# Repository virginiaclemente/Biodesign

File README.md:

# Biodesign
During the Biodesign course, my team and I developed a syringe infusion pump, a mechatronic device to control the flow rate of drug delivery.

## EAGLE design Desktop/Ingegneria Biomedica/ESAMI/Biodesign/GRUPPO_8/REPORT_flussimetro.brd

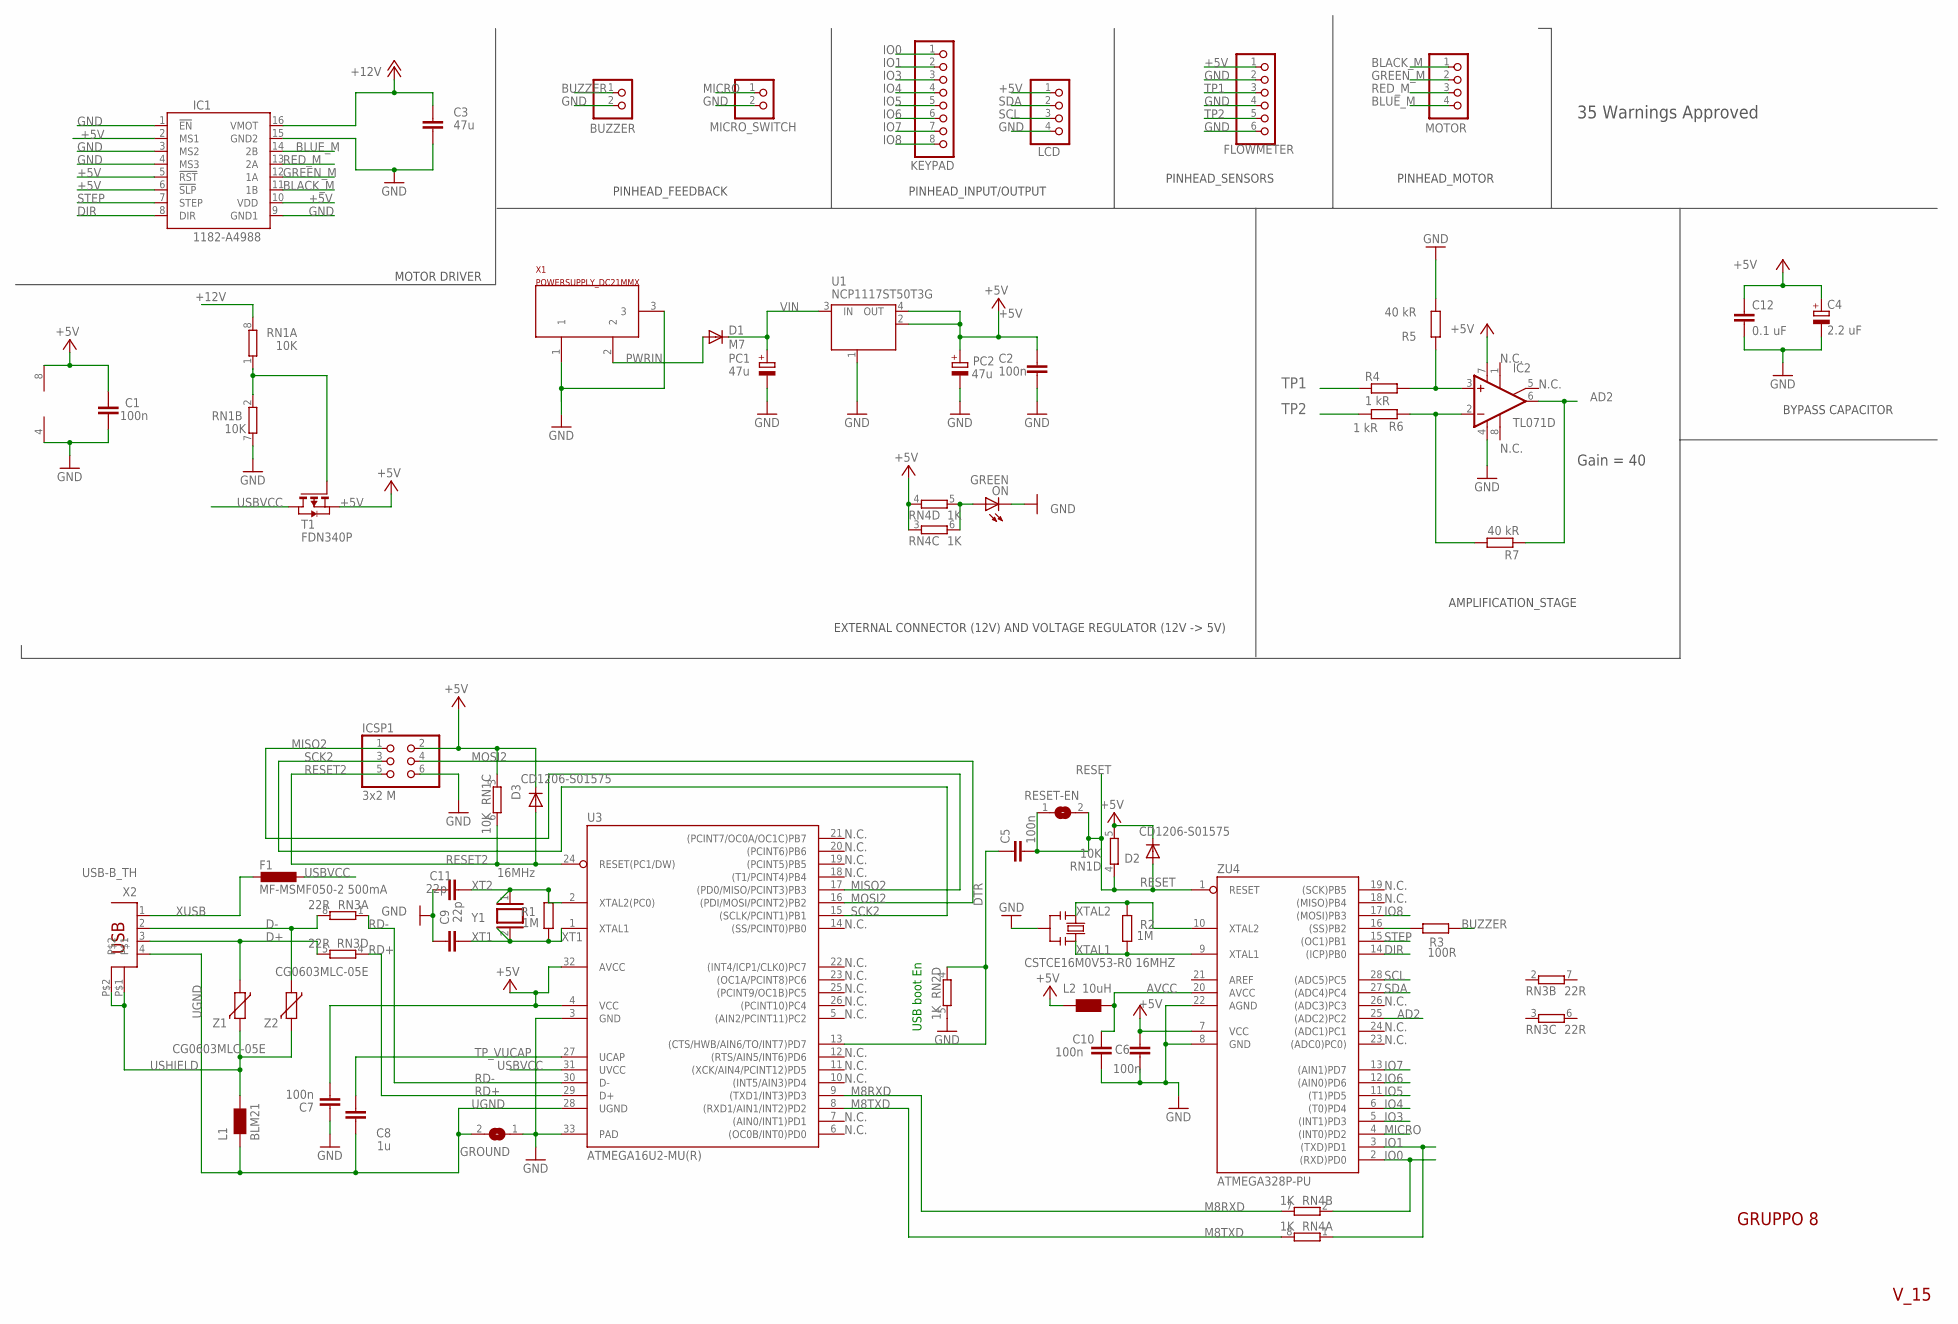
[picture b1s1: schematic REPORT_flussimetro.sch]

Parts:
BUZZER: PINHD-1X2; 1X02; MPN 826926-2
C1, C2, C5, C6, C7, C10: 100n; C0603-ROUND; MPN 4550-10
C3: 47u; C0603; MPN GRM188R60J476ME15D
C4: 2.2 uF; A/3216-18R; MPN TAJA225K016RNJ
C8: 1u; C0603-ROUND; MPN C1608X5R1C105K080AA
C9, C11: 22p; C0603-ROUND; MPN 06035A220FAT2A
C12: 0.1 uF; C0603; MPN 0603YC104KAT2A
D1: M7; SMB; MPN S1M-13-F
D2, D3: CD1206-S01575; MINIMELF; MPN CD1206-S01575
F1: MF-MSMF050-2 500mA; L1812; MPN MF-MSMF050-2
FLOWMETER: PINHD-1X6; 1X06; MPN 2211S-06G
GROUND: SJ
IC1: 1182-A4988; A4988
IC2: TL071D; SO08; MPN LT1211CS8#TRPBF
ICSP1: 3x2 M; 2X03; MPN 87758-0616
KEYPAD: PINHD-1X8; 1X08; MPN 2211S-08G
L1: BLM21; 0805; MPN BLM21SP471BH1D
L2: 10uH; 0805; MPN CV201210-100K
LCD: PINHD-1X4; 1X04; MPN 826926-4
MICRO_SWITCH: PINHD-1X2; 1X02; MPN 826926-2
MOTOR: PINHD-1X4; 1X04; MPN 826926-4
ON: GREEN; CHIP-LED0805; MPN KP-1608SGC
PC1, PC2: 47u; PANASONIC_D; MPN EEE1EA470WP
R1, R2: 1M; R0603-ROUND; MPN CRGH0603J1M0
R3: 100R; R0603; MPN ERJPA3F1000V
R4, R6: 1 kR; R0603; MPN CPF0603B1K0E1
R5, R7: 40 kR; R0603; MPN AT0603BRD0740KL
RESET-EN: SJ
RN1: 10K; CAY16; MPN CAY16-1002F4LF
RN2, RN4: 1K; CAY16; MPN CAY16-102J4LF
RN3: 22R; CAY16; MPN CAY16-220J4LF
T1: FDN340P; SOT-23; MPN FDN340P
U1: NCP1117ST50T3G; SOT223; MPN NCP1117ST50T3G
U3: ATMEGA16U2-MU(R); MLF32; MPN ATMEGA16U2-MUR
U5: LMV358IDGKR; MSOP08; MPN LMV358LIST
X1: POWERSUPPLY_DC21MMX; POWERSUPPLY_DC-21MM; MPN 1613 21
X2: USB-B_TH; PN61729; MPN SPC4937
Y1: 16MHz; QS; MPN ECS-160-20-4X
Y2: CSTCE16M0V53-R0 16MHZ; RESONATOR; MPN CSTNE16M0V51C000R0
Z1, Z2: CG0603MLC-05E; CT/CN0603; MPN CG0603MLC-05E
ZU4: ATMEGA328P-PU; DIL28-3; MPN ATMEGA328P-PU

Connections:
+5V: C1.2, C2.2, C4.+, C6.2, C7.1, C12.1, D2.C, D3.C, FLOWMETER.1, IC1.2 (MS1), IC1.5 (!RST), IC1.6 (!SLP), IC1.10 (VDD), IC2.7 (V+), ICSP1.2, L2.1, LCD.1, PC2.+, RN1.1, RN1.2 (1), RN1.3 (1), RN1.5 (2), RN4.3 (1), RN4.4 (1), T1.2 (S), T1.3 (G), U1.2 (OUT), U1.4 (OUT), U3.4 (VCC), U3.32 (AVCC), U5.8 (V+), ZU4.7 (VCC)
+12V: C3.1, IC1.16 (VMOT), RN1.8 (2)
AD2: IC2.6 (OUT), R7.1, ZU4.25 ((ADC2)PC2)
AVCC: C10.2, L2.2, ZU4.20 (AVCC)
BLACK_M: IC1.11 (1B), MOTOR.1
BLUE_M: IC1.14 (2B), MOTOR.4
BUZZER: BUZZER.1, R3.2
D+: RN3.5 (2), X2.3, Z1.1
D-: RN3.8 (2), X2.2, Z2.1
DIR: IC1.8 (DIR), ZU4.14 ((ICP)PB0)
DTR: C5.1, RN2.4 (1), U3.13 ((CTS/HWB/AIN6/TO/INT7)PD7)
GND: BUZZER.2, C1.1, C2.1, C3.2, C4.-, C6.1, C7.2, C9.2, C10.1, C11.2, C12.2, FLOWMETER.2, FLOWMETER.4, FLOWMETER.6, GROUND.1, IC1.1 (!EN), IC1.3 (MS2), IC1.4 (MS3), IC1.9 (GND1), IC1.15 (GND2), IC2.4 (V-), ICSP1.6, LCD.4, MICRO_SWITCH.2, ON.C, PC1.-, PC2.-, R5.2, RN1.7 (2), RN2.5 (2), U1.1 (GND/ADJ), U3.3 (GND), U3.33 (PAD), U5.4 (V-), X1.1, X1.3, Y2.2, ZU4.8 (GND), ZU4.22 (AGND)
GREEN_M: IC1.12 (1A), MOTOR.2
IO0: KEYPAD.1, RN4.2 (1), ZU4.2 ((RXD)PD0)
IO1: KEYPAD.2, RN4.1, ZU4.3 ((TXD)PD1)
IO3: KEYPAD.3, ZU4.5 ((INT1)PD3)
IO4: KEYPAD.4, ZU4.6 ((T0)PD4)
IO5: KEYPAD.5, ZU4.11 ((T1)PD5)
IO6: KEYPAD.6, ZU4.12 ((AIN0)PD6)
IO7: KEYPAD.7, ZU4.13 ((AIN1)PD7)
IO8: KEYPAD.8, ZU4.17 ((MOSI)PB3)
IO16: R3.1, ZU4.16 ((SS)PB2)
M8RXD: RN4.7 (2), U3.9 ((TXD1/INT3)PD3)
M8TXD: RN4.8 (2), U3.8 ((RXD1/AIN1/INT2)PD2)
MICRO: MICRO_SWITCH.1, ZU4.4 ((INT0)PD2)
MISO2: ICSP1.1, U3.17 ((PD0/MISO/PCINT3)PB3)
MOSI2: ICSP1.4, U3.16 ((PDI/MOSI/PCINT2)PB2)
unnamed: IC2.2 (-IN), R6.1, R7.2
unnamed: IC2.3 (+IN), R4.2, R5.1
unnamed: ON.A, RN4.5 (2), RN4.6 (2)
PWRIN: D1.A, X1.2
RD+: RN3.4 (1), U3.29 (D+)
RD-: RN3.1, U3.30 (D-)
RED_M: IC1.13 (2A), MOTOR.3
RESET: C5.2, D2.A, RESET-EN.1, RESET-EN.2, RN1.4 (1), ZU4.1 (RESET)
RESET2: D3.A, ICSP1.5, RN1.6 (2), U3.24 (RESET(PC1/DW))
SCK2: ICSP1.3, U3.15 ((SCLK/PCINT1)PB1)
SCL: LCD.3, ZU4.28 ((ADC5)PC5)
SDA: LCD.2, ZU4.27 ((ADC4)PC4)
STEP: IC1.7 (STEP), ZU4.15 ((OC1)PB1)
TP1: FLOWMETER.3, R4.1
TP2: FLOWMETER.5, R6.2
TP_VUCAP: C8.1, U3.27 (UCAP)
UGND: C8.2, GROUND.2, L1.1, U3.28 (UGND), X2.4
USBVCC: F1.1, T1.1 (D), U3.31 (UVCC)
USHIELD: L1.2, X2.P$1, X2.P$2, Z1.2, Z2.2
VIN: D1.C, PC1.+, U1.3 (IN)
XT1: C9.1, R1.1, U3.1 (XTAL1), Y1.2
XT2: C11.1, R1.2, U3.2 (XTAL2(PC0)), Y1.1
XTAL1: R2.1, Y2.3, ZU4.9 (XTAL1)
XTAL2: R2.2, Y2.1, ZU4.10 (XTAL2)
XUSB: F1.2, X2.1

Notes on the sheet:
USB boot En
GRUPPO 8
V_15
MOTOR DRIVER
PINHEAD_FEEDBACK
PINHEAD_INPUT/OUTPUT
PINHEAD_SENSORS
PINHEAD_MOTOR
EXTERNAL CONNECTOR (12V) AND VOLTAGE REGULATOR (12V -> 5V)
N.C.
35 Warnings Approved
AMPLIFICATION_STAGE
Gain = 40
BYPASS CAPACITOR

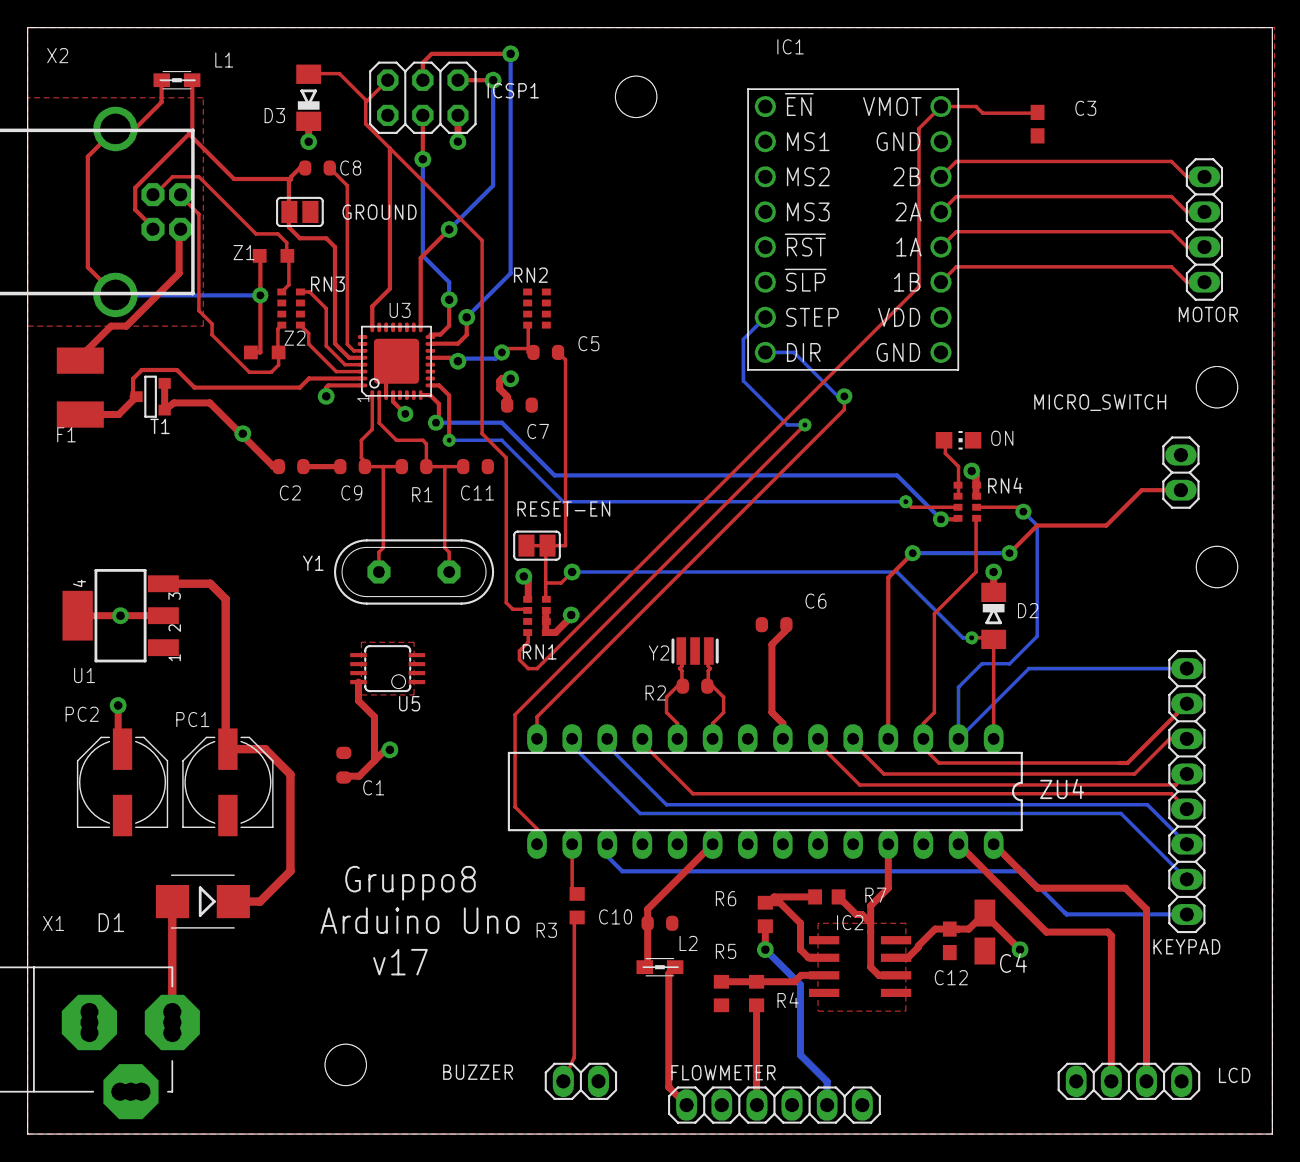
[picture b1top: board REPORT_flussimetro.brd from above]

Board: 2 copper layers, 90.0 x 80.0 mm, 54 parts (0 on the bottom side), 52 nets.
